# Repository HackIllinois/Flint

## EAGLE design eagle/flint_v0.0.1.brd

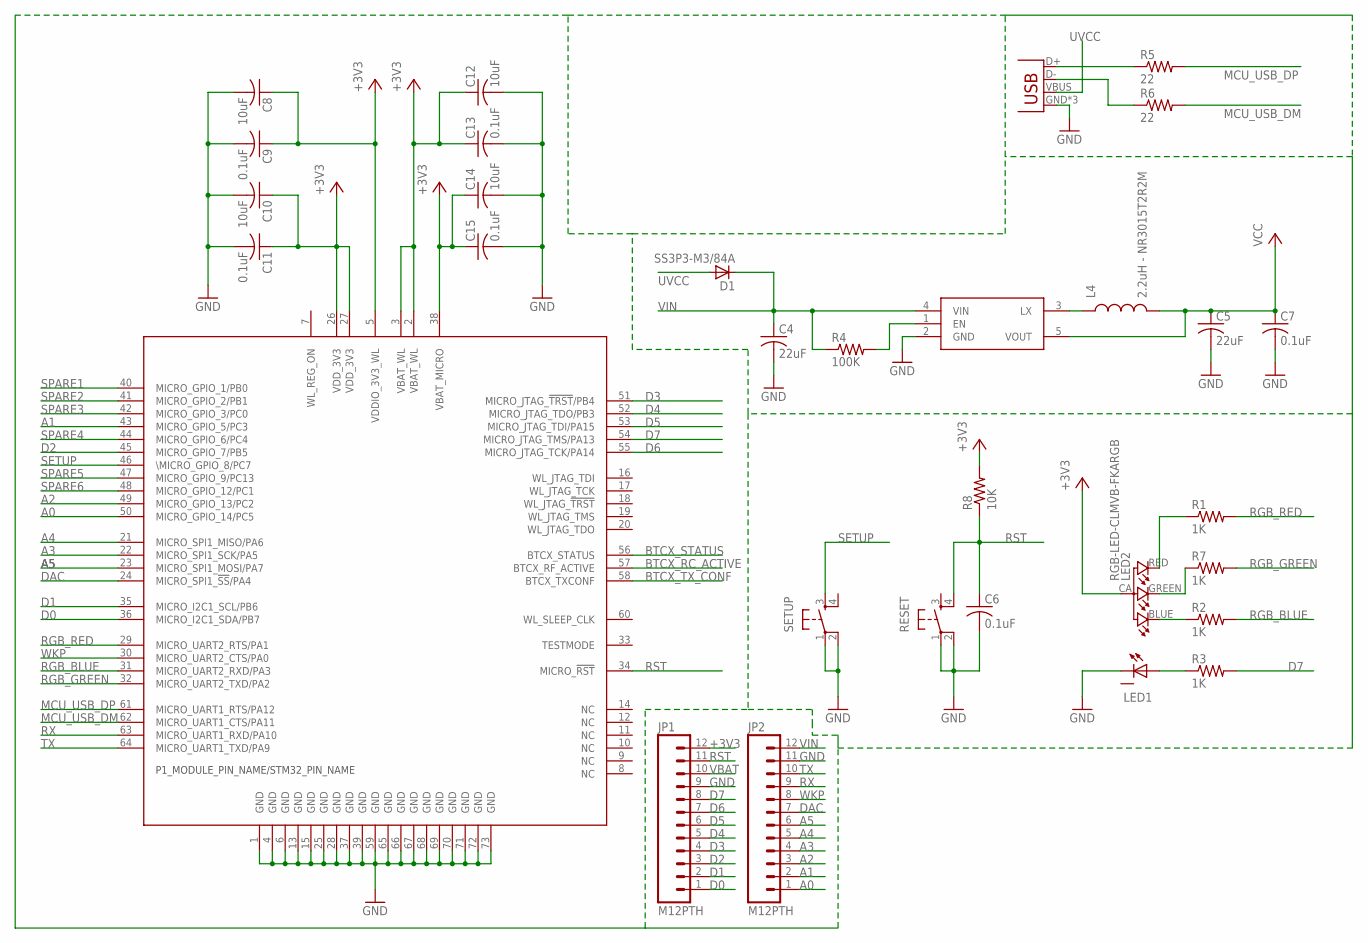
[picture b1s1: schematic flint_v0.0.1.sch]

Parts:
C4, C5: 22uF; C0402_B
C6, C7, C9, C11, C13, C15: 0.1uF; C0402_B
C8, C10, C12, C14: 10uF; C0402_B
D1: SS3P3-M3/84A; SOD106A
JP1, JP2: M12PTH; 1X12-SMALL-PADS
JP4: USBUSB-MICROB-SMT-DIP; USB-MICROB-SMT-DIP
L4: 2.2uH - NR3015T2R2M; INDUCTOR-NR3015
LED1: BLUE; CREE_XLAMP
LED2: RGB-LED-CLMVB-FKARGB; PLCC4-2MM-RGB
R1, R2, R3, R7: 1K; R0402_B
R4: 100K; R0402_B
R5, R6: 22; R0402_B
R8: 10K; R0402_B
RESET: TAC_SWITCHSMD; TACTILE_SWITCH_SMD
SETUP: TAC_SWITCHSMD; TACTILE_SWITCH_SMD
U$1: WM-N-BM-14
U$2: R8008-33; SOT23-5

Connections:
+3V3: C5.1, C7.1, C8.1, C9.1, C10.1, C11.1, C12.1, C13.1, C14.1, C15.1, JP1.12, L4.2, LED2.CA (1), R8.2, U$1.2 (VBAT_WL), U$1.3 (VBAT_WL), U$1.5 (VDDIO_3V3_WL), U$1.26 (VDD_3V3), U$1.27 (VDD_3V3), U$1.38 (VBAT_MICRO), U$2.5 (VOUT)
A0: JP2.1, U$1.50 (MICRO_GPIO_14/PC5)
A1: JP2.2, U$1.43 (MICRO_GPIO_5/PC3)
A2: JP2.3, U$1.49 (MICRO_GPIO_13/PC2)
A3: JP2.4, U$1.22 (MICRO_SPI1_SCK/PA5)
A4: JP2.5, U$1.21 (MICRO_SPI1_MISO/PA6)
A5: JP2.6, U$1.23 (MICRO_SPI1_MOSI/PA7)
BTCX_RC_ACTIVE: U$1.57 (BTCX_RF_ACTIVE)
BTCX_STATUS: U$1.56 (BTCX_STATUS)
BTCX_TX_CONF: U$1.58 (BTCX_TXCONF)
D0: JP1.1, U$1.36 (MICRO_I2C1_SDA/PB7)
D1: JP1.2, U$1.35 (MICRO_I2C1_SCL/PB6)
D2: JP1.3, U$1.45 (MICRO_GPIO_7/PB5)
D3: JP1.4, U$1.51 (MICRO_JTAG_!TRST!/PB4)
D4: JP1.5, U$1.52 (MICRO_JTAG_TDO/PB3)
D5: JP1.6, U$1.53 (MICRO_JTAG_TDI/PA15)
D6: JP1.7, U$1.55 (MICRO_JTAG_TCK/PA14)
D7: JP1.8, R3.2, U$1.54 (MICRO_JTAG_TMS/PA13)
DAC: JP2.7, U$1.24 (MICRO_SPI1_!SS!/PA4)
GND: C4.2, C5.2, C6.2, C7.2, C8.2, C9.2, C10.2, C11.2, C12.2, C13.2, C14.2, C15.2, JP1.9, JP2.11, JP4.GND, JP4.MT1 (GND), JP4.MT2 (GND), LED1.C, LED1.C@1 (C), RESET.1, RESET.2, SETUP.1, SETUP.2, U$1.1 (GND), U$1.4 (GND), U$1.6 (GND), U$1.13 (GND), U$1.15 (GND), U$1.25 (GND), U$1.28 (GND), U$1.37 (GND), U$1.39 (GND), U$1.59 (GND), U$1.65 (GND), U$1.66 (GND), U$1.67 (GND), U$1.68 (GND), U$1.69 (GND), U$1.70 (GND), U$1.71 (GND), U$1.72 (GND), U$1.73 (GND), U$2.2 (GND)
MCU_USB_DM: R6.2, U$1.62 (MICRO_UART1_CTS/PA11)
MCU_USB_DP: R5.2, U$1.61 (MICRO_UART1_RTS/PA12)
unnamed: JP4.D+, R5.1
unnamed: JP4.D-, R6.1
unnamed: R4.2, U$2.1 (EN)
unnamed: LED2.BLUE (2), R2.1
unnamed: L4.1, U$2.3 (LX)
unnamed: LED2.RED (4), R1.1
unnamed: LED2.GREEN (3), R7.1
unnamed: LED1.A, LED1.A@1 (A), R3.1
RGB_BLUE: R2.2, U$1.31 (MICRO_UART2_RXD/PA3)
RGB_GREEN: R7.2, U$1.32 (MICRO_UART2_TXD/PA2)
RGB_RED: R1.2, U$1.29 (MICRO_UART2_RTS/PA1)
RST: C6.1, JP1.11, R8.1, RESET.4, U$1.34 (MICRO_!RST!)
RX: JP2.9, U$1.63 (MICRO_UART1_RXD/PA10)
SETUP: SETUP.3, U$1.46 (\MICRO_GPIO_8/PC7)
SPARE1: U$1.40 (MICRO_GPIO_1/PB0)
SPARE2: U$1.41 (MICRO_GPIO_2/PB1)
SPARE3: U$1.42 (MICRO_GPIO_3/PC0)
SPARE4: U$1.44 (MICRO_GPIO_6/PC4)
SPARE5: U$1.47 (MICRO_GPIO_9/PC13)
SPARE6: U$1.48 (MICRO_GPIO_12/PC1)
TX: JP2.10, U$1.64 (MICRO_UART1_TXD/PA9)
UVCC: D1.A, JP4.VBUS
VBAT: JP1.10
VIN: C4.1, D1.K, JP2.12, R4.1, U$2.4 (VIN)
WKP: JP2.8, U$1.30 (MICRO_UART2_CTS/PA0)

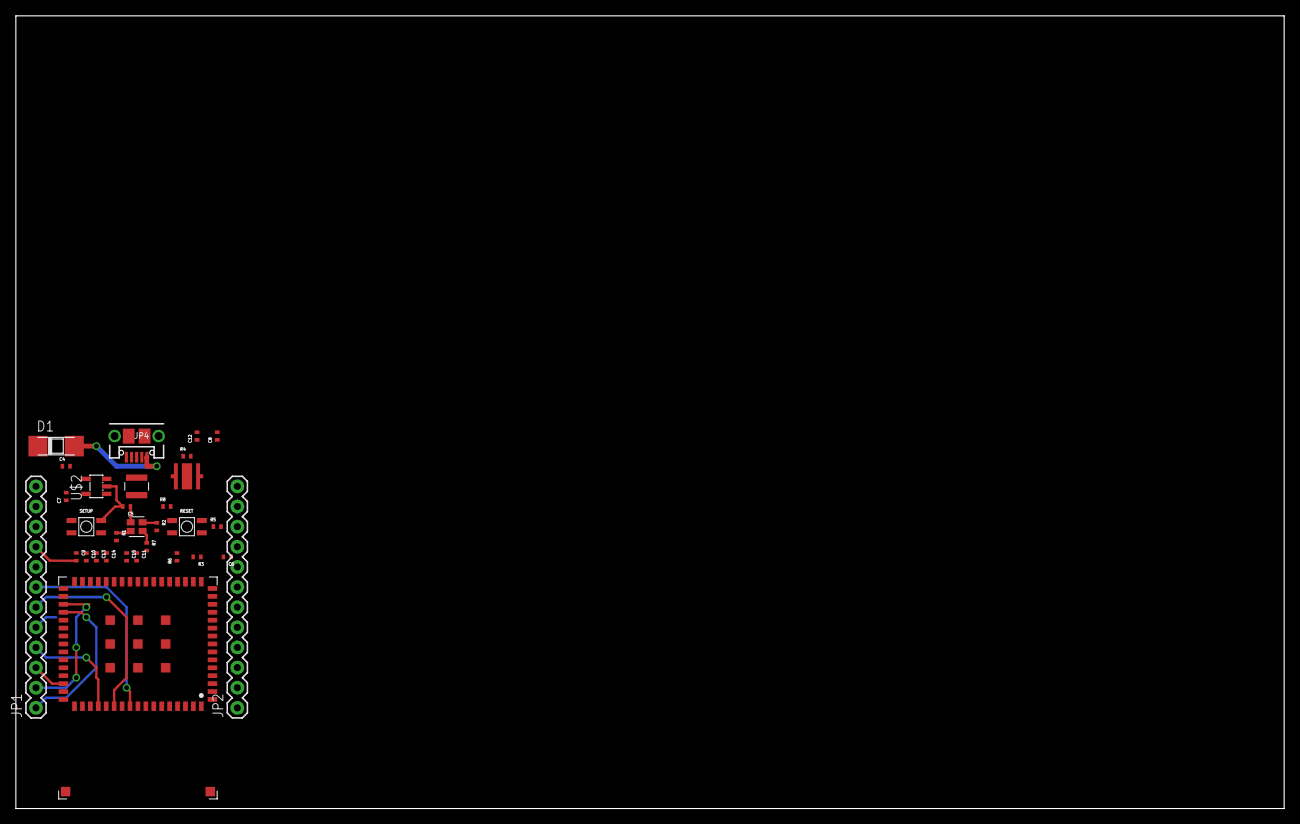
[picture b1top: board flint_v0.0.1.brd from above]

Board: 2 copper layers, 160.0 x 100.0 mm, 31 parts (0 on the bottom side), 37 nets.

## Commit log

2015-09-29 schmatic minus sensors
2015-10-15 eagle gitignore
    do this
